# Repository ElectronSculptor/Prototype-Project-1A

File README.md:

# Variable Distance Digital Code Lock

This project involves designing a contactless, proximity-based digital code lock system that uses capacitive sensors to detect the distance of a user’s hand from the sensors. The lock system supports complex, multi-position authentication codes that enhance security while maintaining hygiene by eliminating physical contact.

## Date

- September 15, 2024

## Project Objectives

The goal of the project was to address the limitations of traditional digital code locks, such as susceptibility to code theft through button wear and the potential transmission of bacteria. This new system offers:
- **Improved Security**: The system allows for more complex combinations by detecting the proximity of the user's hand to sensors, making it harder to steal access codes.
- **Hygiene**: A contactless interface reduces the risk of transmitting diseases.
- **Intuitiveness**: The system is easy to use with a simple, natural interface.

## Key Components

### 1. Capacitive Sensors
The system uses capacitive sensors to detect proximity and distinguish between two positions: near and far.

### 2. Signal Conditioning Circuit
The conditioner processes signals from the sensors using:
- Constant current charging for accurate capacitance measurement.
- An oscillator with a hysteresis comparator to detect the proximity threshold.

### 3. STM32 Microcontroller
An STM32 microcontroller handles the acquisition and processing of capacitance signals, converting them into digital data and determining combinations of sensor inputs.

### 4. PCB Design
The project’s electronics were designed using KiCAD to create a printed circuit board (PCB) integrating the sensors, microcontroller, and related components.

## System Architecture

1. **Capacitive Sensors**: Detect hand proximity in two positions (near/far).
2. **Conditioner**: A signal conditioner charges the capacitors and measures the charging time to deduce proximity.
3. **STM32 Microcontroller**: Handles the signal acquisition and processes input data for the multi-position code lock system.

## Testing and Results

- Testing was performed using the designed conditioners and the STM32.
- The system successfully detected two positions (near and far) and responded by lighting up LEDs in different colors to confirm the correct hand position.
- A servo motor was used as the final actuator to simulate opening a door.

## Challenges and Solutions

### PCB Design Issues
- The initial PCB design could not be fully tested due to a shortage of components.
- A revised routing method using pre-made conditioners was adopted to address manufacturing issues.

### Signal Acquisition
- Various issues were encountered with signal acquisition due to UART configuration, which was solved by using alternative UART ports.

## Conclusion

Although some objectives were not fully achieved due to technical difficulties, the project demonstrates significant progress in creating a secure, intuitive, and contactless digital code lock. Further improvements can be made in:
- Optimizing the conditioner for better detection range.
- Enhancing the user interface for ease of use.
- Expanding the application to other access control systems.

## Appendices

1. **Capacitor Code for PartQuest Simulation**
2. **STM32 Microcontroller Code**
3. **Demonstrations and Additional Calculations**

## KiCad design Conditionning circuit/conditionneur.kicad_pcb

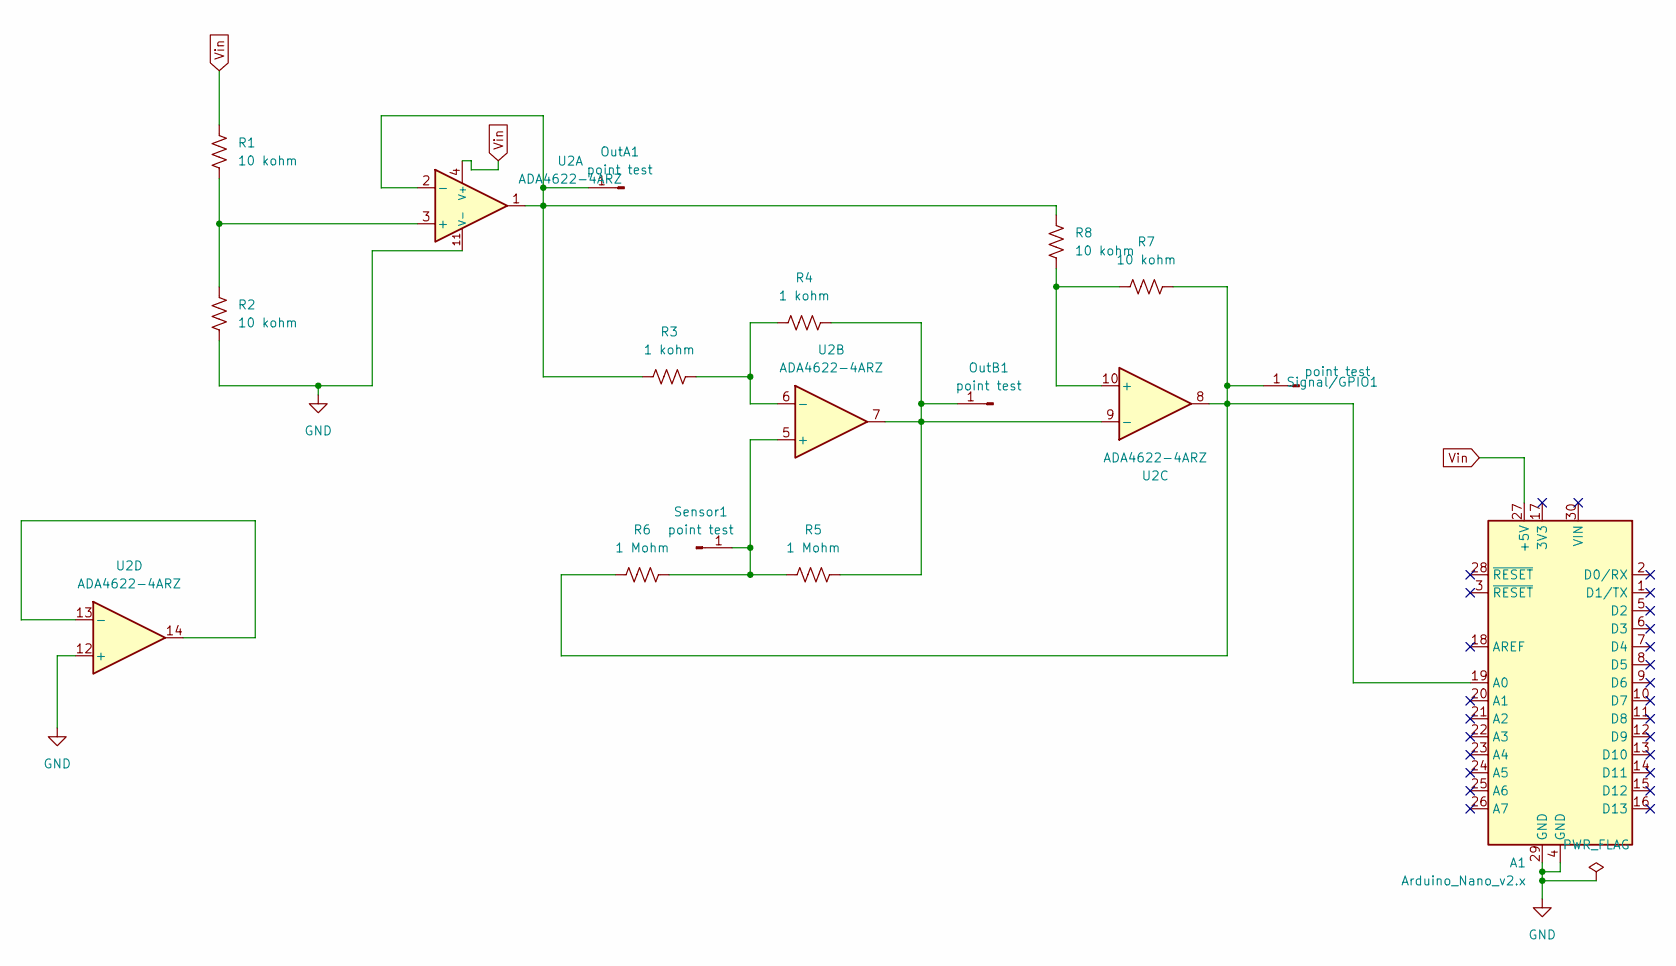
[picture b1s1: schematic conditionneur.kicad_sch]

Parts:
A1: Arduino_Nano_v2.x; Arduino_Nano
OutA1: point test; PinHeader_1x01_P2.54mm_Vertical
OutB1: point test; PinHeader_1x01_P2.54mm_Vertical
R1, R2, R7, R8: 10 kohm; R_0805_2012Metric_Pad1.20x1.40mm_HandSolder
R3, R4: 1 kohm; R_0805_2012Metric_Pad1.20x1.40mm_HandSolder
R5, R6: 1 Mohm; R_0805_2012Metric_Pad1.20x1.40mm_HandSolder
Sensor1: point test; PinHeader_1x01_P2.54mm_Vertical
Signal/GPIO1: point test; PinHeader_1x01_P2.54mm_Vertical
U2: ADA4622-4ARZ; SOIC-14_3.9x8.7mm_P1.27mm

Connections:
GND: A1.4 (GND), A1.29 (GND), R2.2, U2.11 (V-), U2.12 (+)
unnamed: A1.19 (A0), R6.2, R7.1, Signal/GPIO1.1, U2.8
unnamed: OutA1.1, R3.2, R8.1, U2.1, U2.2 (-)
unnamed: OutB1.1, R4.1, R5.1, U2.7, U2.9 (-)
unnamed: R5.2, R6.1, Sensor1.1, U2.5 (+)
unnamed: R1.2, R2.1, U2.3 (+)
unnamed: R3.1, R4.2, U2.6 (-)
unnamed: R7.2, R8.2, U2.10 (+)
unnamed: U2.13 (-), U2.14
Vin: A1.27 (+5V), R1.1, U2.4 (V+)

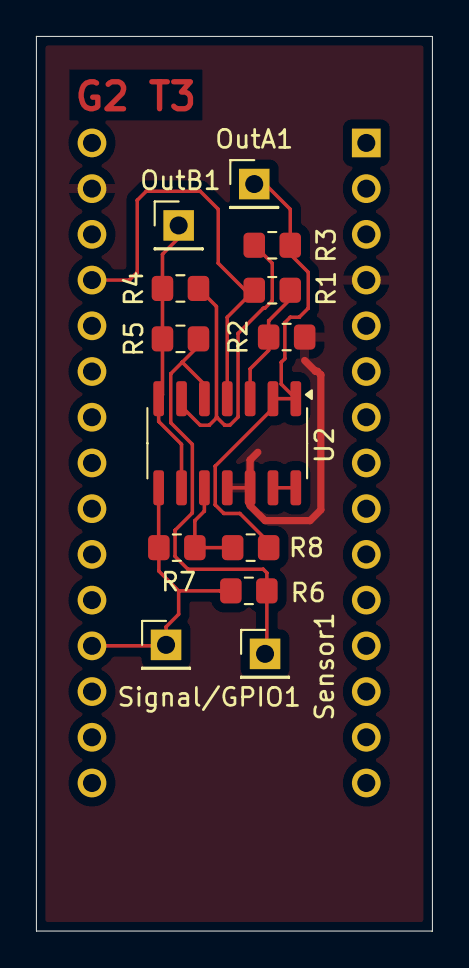
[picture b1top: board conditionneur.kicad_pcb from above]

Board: 2 copper layers, 22.0 x 49.7 mm, 14 parts (1 on the bottom side), 10 nets.
